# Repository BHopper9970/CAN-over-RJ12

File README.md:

# CAN-over-RJ12
A PCB project for carrying CANbus, power and Digital IO over RJ45 wires, primarily for FRC robotics

This repository includes the Kicad Project files for all PCBs (excluding the regulator – designed in EasyEDA) as well as gerber files (exported for JLC, may work with other manufacturers) and 3D models for all PCBs

To Do:
- fix rio hub regulator retention hole
- add DIO passthough to Rio module
- others

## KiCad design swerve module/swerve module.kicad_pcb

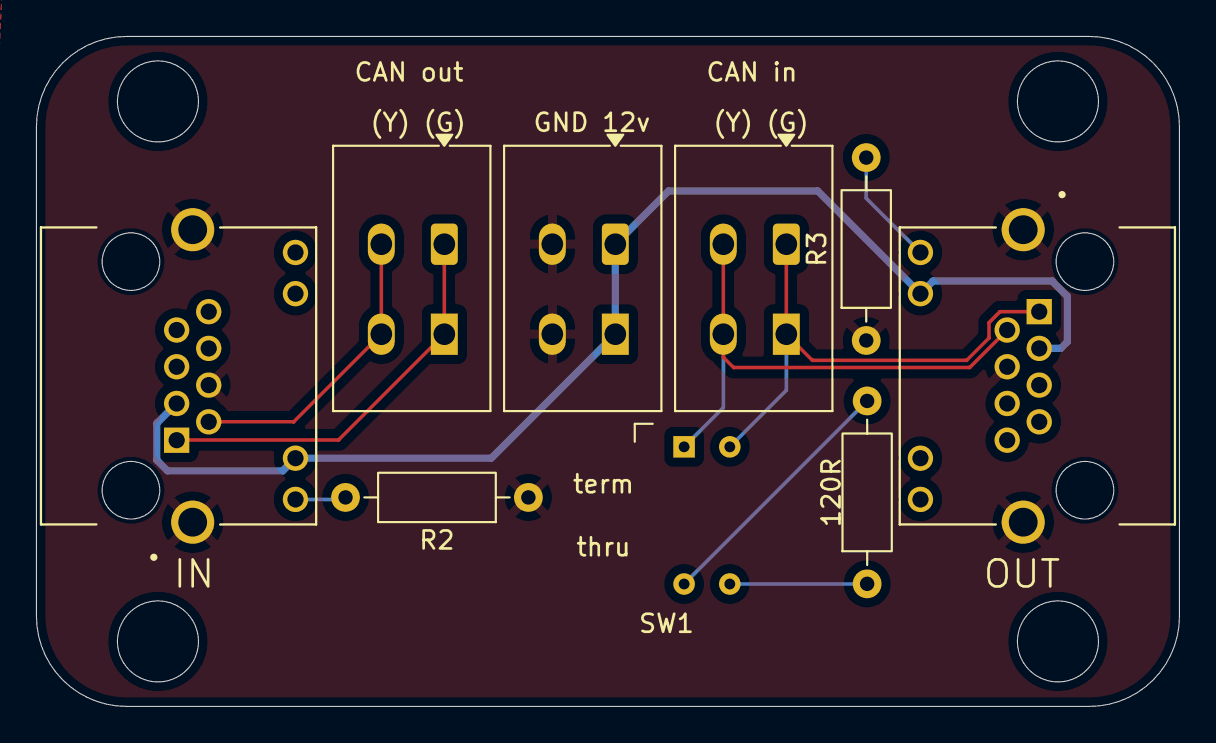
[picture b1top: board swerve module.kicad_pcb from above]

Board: 2 copper layers, 63.5 x 37.2 mm, 9 parts (0 on the bottom side), 10 nets.

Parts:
120R: 120R; R_Axial_DIN0207_L6.3mm_D2.5mm_P10.16mm_Horizontal
J1, J2: MTJ-88ARX1-FSM-LG; ADAMTECH_MTJ-88ARX1-FSM-LG
J3: CAN out; TerminalBlock_WAGO_2601-1102_1x02_P3.50mm_Horizontal w-model
J4: 12v; TerminalBlock_WAGO_2601-1102_1x02_P3.50mm_Horizontal w-model
J5: CAN in; TerminalBlock_WAGO_2601-1102_1x02_P3.50mm_Horizontal w-model
R2, R3: R; R_Axial_DIN0207_L6.3mm_D2.5mm_P10.16mm_Horizontal
SW1: SW_DPST; 206-211

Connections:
/12v: J1.3, J1.10, J2.3, J2.10, J4.1
/CANh: J1.1, J3.1
/CANl: J1.2, J3.2
/GND: J1.4, J1.SH1 (SHIELD), J1.SH2 (SHIELD__1), J2.4, J2.SH1 (SHIELD), J2.SH2 (SHIELD__1), J4.2, R2.1, R3.1
unnamed: J1.9, R2.2
unnamed: J2.9, R3.2
unnamed: J2.1, J5.1, SW1.3
unnamed: J2.2, J5.2, SW1.1
unnamed: 120R.1, SW1.4
unnamed: 120R.2, SW1.2

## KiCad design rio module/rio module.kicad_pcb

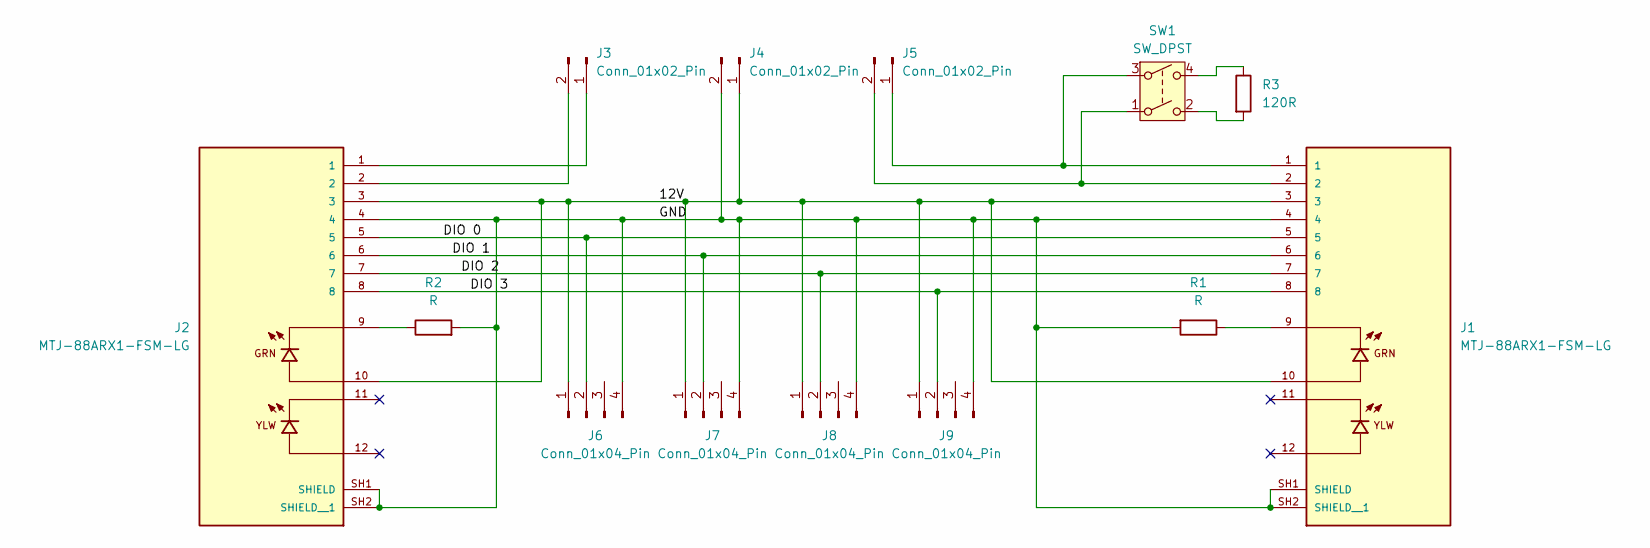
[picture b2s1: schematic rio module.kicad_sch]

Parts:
J1, J2: MTJ-88ARX1-FSM-LG; ADAMTECH_MTJ-88ARX1-FSM-LG; PARTREV H
J3, J4, J5: Conn_01x02_Pin; TerminalBlock_WAGO_2601-1102_1x02_P3.50mm_Horizontal w-model
J6, J7, J8, J9: Conn_01x04_Pin; Molex_SL_171971-0004_1x04_P2.54mm_Vertical
R1, R2: R; R_Axial_DIN0207_L6.3mm_D2.5mm_P10.16mm_Horizontal
R3: 120R; R_Axial_DIN0207_L6.3mm_D2.5mm_P10.16mm_Horizontal
SW1: SW_DPST; 206-211

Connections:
/12V: J1.3, J1.10, J2.3, J2.10, J4.1, J6.1, J7.1, J8.1, J9.1
/DIO 0: J1.5, J2.5, J6.2
/DIO 1: J1.6, J2.6, J7.2
/DIO 2: J1.7, J2.7, J8.2
/DIO 3: J1.8, J2.8, J9.2
/GND: J1.4, J1.SH1 (SHIELD), J1.SH2 (SHIELD__1), J2.4, J2.SH1 (SHIELD), J2.SH2 (SHIELD__1), J4.2, J6.4, J7.4, J8.4, J9.4, R1.2, R2.2
DIO0_C: J8.3
DIO1_C: J9.3
DIO2_C: J6.3
DIO3_C: J7.3
unnamed: J1.9, R1.1
unnamed: J2.9, R2.1
unnamed: J2.1, J3.1
unnamed: J2.2, J3.2
unnamed: J1.1, J5.1, SW1.3
unnamed: J1.2, J5.2, SW1.1
unnamed: R3.1, SW1.4
unnamed: R3.2, SW1.2

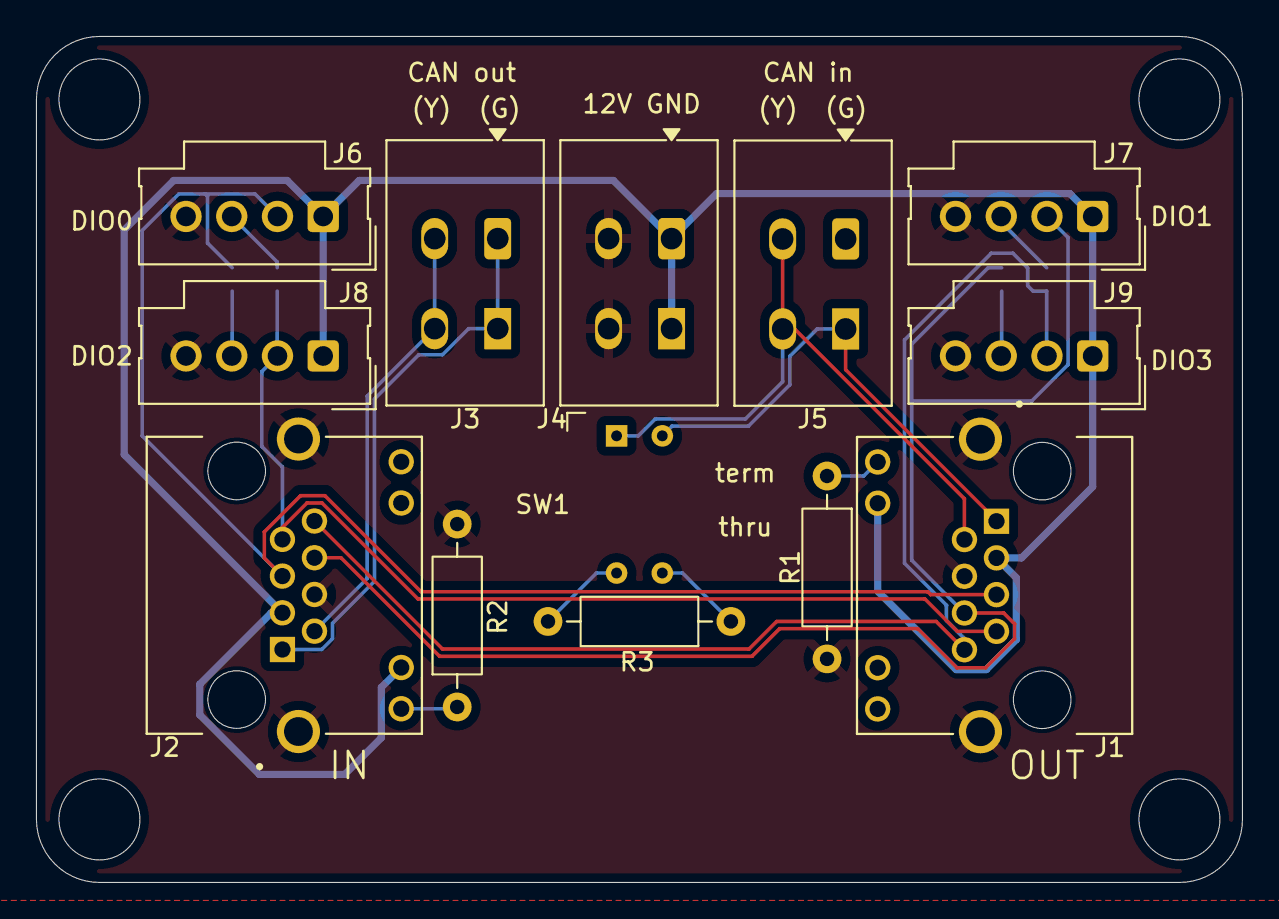
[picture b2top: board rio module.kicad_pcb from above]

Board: 2 copper layers, 67.0 x 47.0 mm, 13 parts (0 on the bottom side), 14 nets.

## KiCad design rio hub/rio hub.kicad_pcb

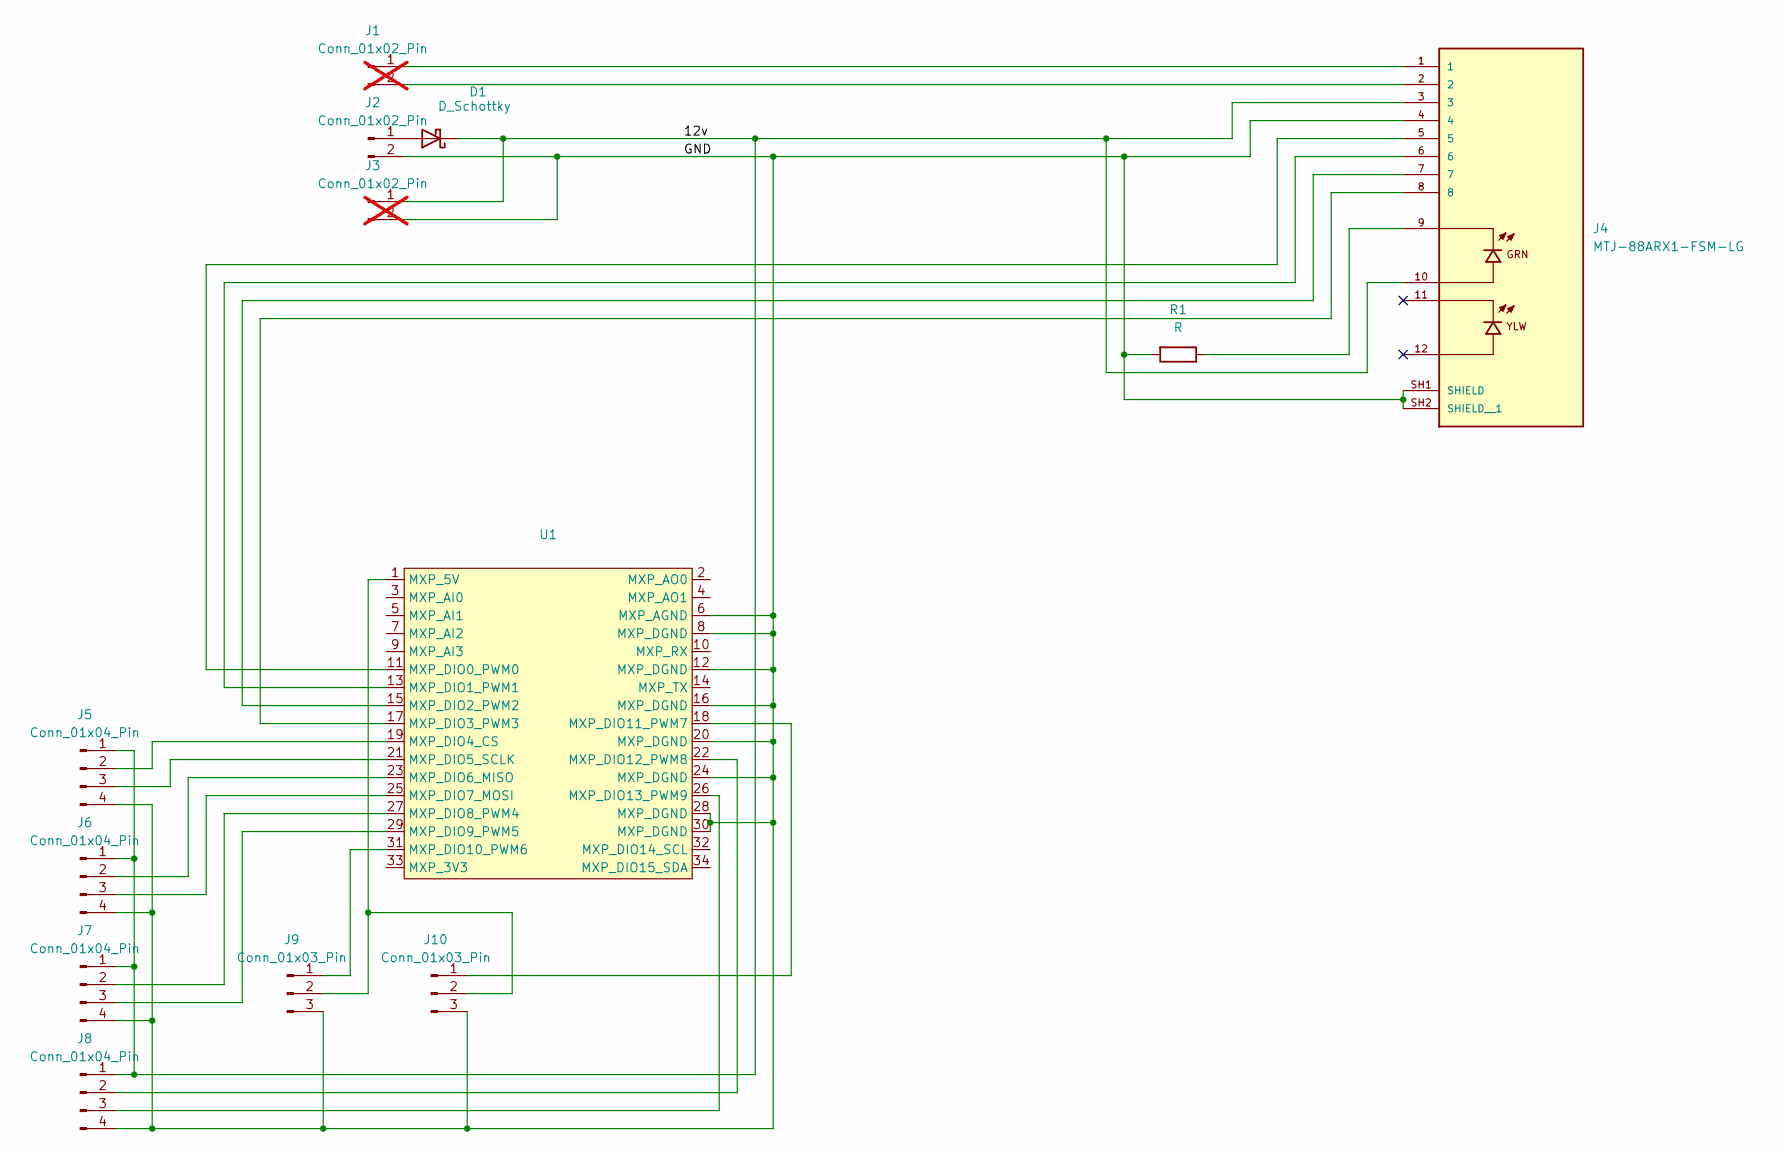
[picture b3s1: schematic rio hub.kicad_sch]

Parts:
D1: D_Schottky; D_DO-41_SOD81_P10.16mm_Horizontal
J1, J3: Conn_01x02_Pin; PinHeader_1x02_P2.54mm_Vertical; not fitted
J2: Conn_01x02_Pin; TerminalBlock_WAGO_2601-1102_1x02_P3.50mm_Horizontal
J4: MTJ-88ARX1-FSM-LG; ADAMTECH_MTJ-88ARX1-FSM-LG; PARTREV H
J5, J6, J7, J8: Conn_01x04_Pin; Molex_SL_171971-0004_1x04_P2.54mm_Vertical
J9, J10: Conn_01x03_Pin; Molex_SL_171971-0003_1x03_P2.54mm_Vertical
R1: R; R_Axial_DIN0207_L6.3mm_D2.5mm_P10.16mm_Horizontal
U1: RoboRIO_MXP-THT

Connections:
/GND: J2.2, J3.2, J4.4, J4.SH1 (SHIELD), J4.SH2 (SHIELD__1), J5.4, J6.4, J7.4, J8.4, J9.3, J10.3, R1.2, U1.6 (MXP_AGND), U1.8 (MXP_DGND), U1.12 (MXP_DGND), U1.16 (MXP_DGND), U1.20 (MXP_DGND), U1.24 (MXP_DGND), U1.28 (MXP_DGND), U1.30 (MXP_DGND)
unnamed: D1.2 (A), J2.1
unnamed: J1.1, J4.1
unnamed: J1.2, J4.2
unnamed: J4.9, R1.1
unnamed: J5.2, U1.19 (MXP_DIO4_CS)
unnamed: J5.3, U1.21 (MXP_DIO5_SCLK)
unnamed: J6.2, U1.23 (MXP_DIO6_MISO)
unnamed: J6.3, U1.25 (MXP_DIO7_MOSI)
unnamed: J7.2, U1.27 (MXP_DIO8_PWM4)
unnamed: J7.3, U1.29 (MXP_DIO9_PWM5)
unnamed: J8.2, U1.22 (MXP_DIO12_PWM8)
unnamed: J8.3, U1.26 (MXP_DIO13_PWM9)
unnamed: J9.1, U1.31 (MXP_DIO10_PWM6)
unnamed: J10.1, U1.18 (MXP_DIO11_PWM7)
unnamed: J9.2, J10.2, U1.1 (MXP_5V)
unnamed: J4.5, U1.11 (MXP_DIO0_PWM0)
unnamed: J4.6, U1.13 (MXP_DIO1_PWM1)
unnamed: J4.7, U1.15 (MXP_DIO2_PWM2)
unnamed: J4.8, U1.17 (MXP_DIO3_PWM3)

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
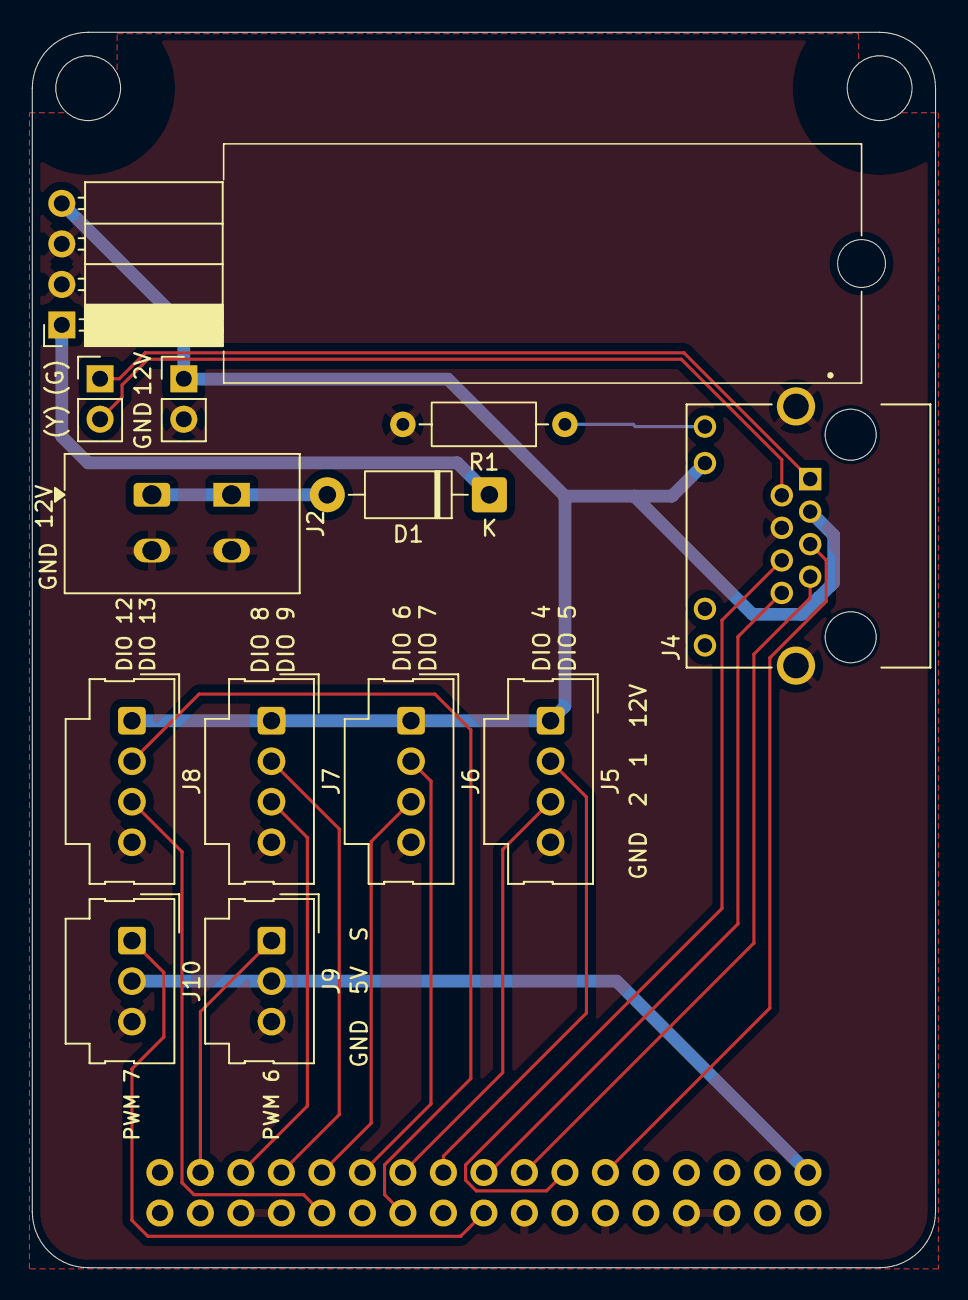
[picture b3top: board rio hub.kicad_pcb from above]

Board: 2 copper layers, 56.6 x 77.5 mm, 13 parts (0 on the bottom side), 21 nets.

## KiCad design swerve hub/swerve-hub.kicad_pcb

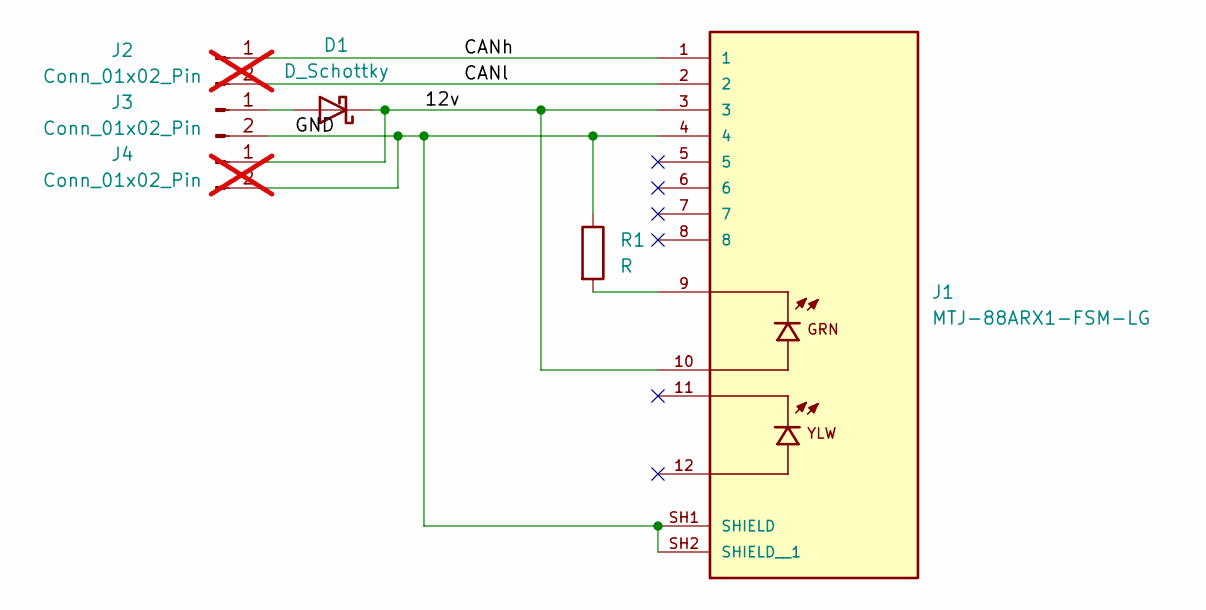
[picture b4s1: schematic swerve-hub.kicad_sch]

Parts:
D1: D_Schottky; D_DO-41_SOD81_P10.16mm_Horizontal
J1: MTJ-88ARX1-FSM-LG; ADAMTECH_MTJ-88ARX1-FSM-LG; PARTREV H
J2, J4: Conn_01x02_Pin; PinHeader_1x02_P2.54mm_Vertical; not fitted
J3: Conn_01x02_Pin; TerminalBlock_WAGO_2601-1102_1x02_P3.50mm_Horizontal
R1: R; R_Axial_DIN0207_L6.3mm_D2.5mm_P10.16mm_Horizontal

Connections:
/12v: D1.1 (K), J1.3, J1.10, J4.1
/CANh: J1.1, J2.1
/CANl: J1.2, J2.2
/GND: J1.4, J1.SH1 (SHIELD), J1.SH2 (SHIELD__1), J3.2, J4.2, R1.1
unnamed: D1.2 (A), J3.1
unnamed: J1.9, R1.2

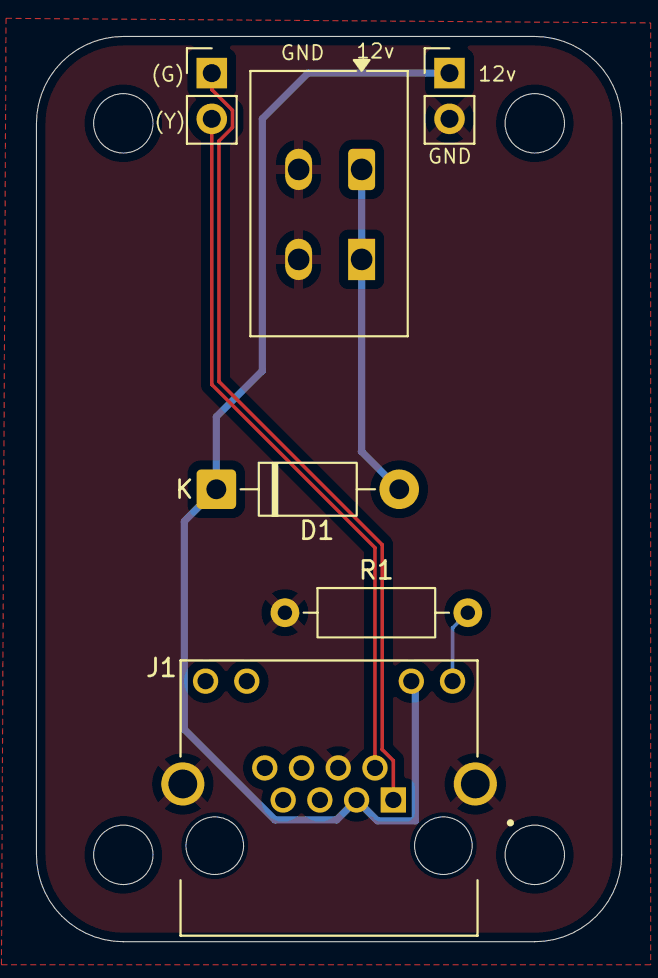
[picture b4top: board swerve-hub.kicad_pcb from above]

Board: 2 copper layers, 32.5 x 50.3 mm, 6 parts (0 on the bottom side), 6 nets.

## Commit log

2025-10-23 reorganised project and started swerve bus
2025-10-23 canivore hub mostly done
2025-10-24 Swerve Hub PCB work
2025-10-24 swerve hub pcb rearrange and added reverse polarity protection
2025-10-25 swerve can improvements, ground planes, removed excess wagos
2025-10-25 started rio can
2025-10-26 fixed diode placement, major rio hub work
2025-10-29 rio hub work
2025-10-29 rio module and added better silkscreening
2025-11-13 removed mxp crossover, moved to hardwired DIO, switching from DIO WAGOs to Molex SL
2025-11-13 added features claimed to be from previous commit
2025-11-18 in a rush, changes made
2025-11-18 final major changes, exported for JLCPCB
2025-12-07 added 3d models
2025-12-29 added regulator gerbers and updated readme
2025-12-29 Create LICENSE
2025-12-30 added photos and updated todo
2025-12-30 removed switch from swerve module photo
2025-12-30 added regulator photos
